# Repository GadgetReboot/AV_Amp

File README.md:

# AV_Amp
THS7316 three channel video buffer and stereo op amp audio buffer
<br><br><BR><BR>

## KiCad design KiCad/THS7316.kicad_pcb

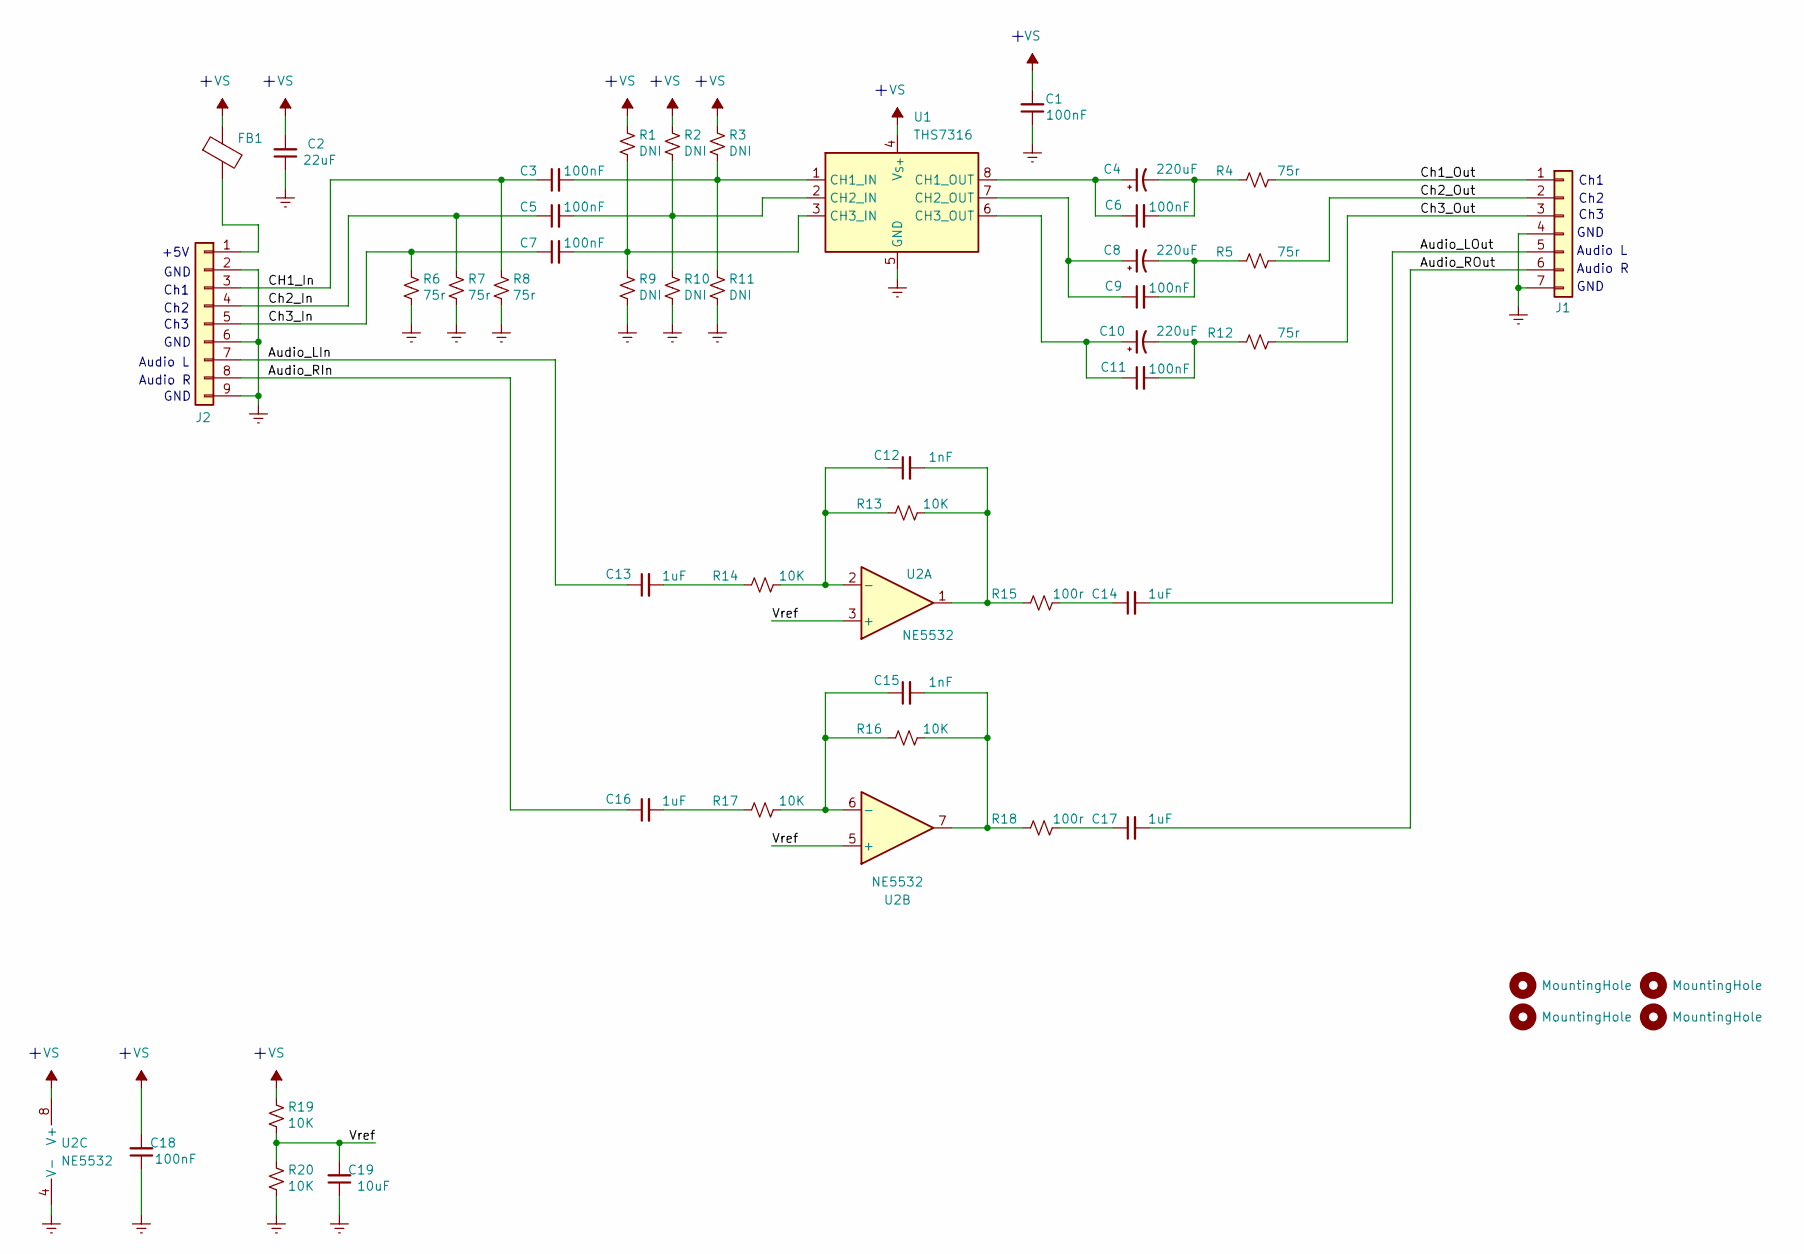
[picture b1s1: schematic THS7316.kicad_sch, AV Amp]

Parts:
C1, C3, C5, C6, C7, C9, C11, C18: 100nF; C_0805_2012Metric_Pad1.18x1.45mm_HandSolder
C2: 22uF; C_0805_2012Metric_Pad1.18x1.45mm_HandSolder
C4, C8, C10: 220uF; CP_Elec_6.3x7.7; MPN EDK227M010A9HAA
C12, C15: 1nF; C_0805_2012Metric_Pad1.18x1.45mm_HandSolder
C13, C14, C16, C17: 1uF; C_0805_2012Metric_Pad1.18x1.45mm_HandSolder
C19: 10uF; C_0805_2012Metric_Pad1.18x1.45mm_HandSolder
FB1: MPZ2012S331A; L_0805_TDK_MPZ2012S331A
H1, H2, H3, H4: MountingHole; MountingHole_3.5mm
J1: Conn_01x07; PinHeader_1x07_P2.54mm_Vertical
J2: Conn_01x09; PinHeader_1x09_P2.54mm_Vertical
R1, R2, R3, R9, R10, R11: DNI; R_0805_2012Metric_Pad1.20x1.40mm_HandSolder
R4, R5, R6, R7, R8, R12: 75r; R_0805_2012Metric_Pad1.20x1.40mm_HandSolder
R13, R14, R16, R17, R19, R20: 10K; R_0805_2012Metric_Pad1.20x1.40mm_HandSolder
R15, R18: 100r; R_0805_2012Metric_Pad1.20x1.40mm_HandSolder
U1: THS7316; SOIC-8_3.9x4.9mm_P1.27mm
U2: NE5532; SOIC-8_3.9x4.9mm_P1.27mm

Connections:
/Audio_LIn: C13.1, J2.7
/Audio_LOut: C14.2, J1.5
/Audio_RIn: C16.1, J2.8
/Audio_ROut: C17.2, J1.6
/CH1_In: C3.1, J2.3, R8.1
/Ch1_Out: J1.1, R4.2
/Ch2_In: C5.1, J2.4, R7.1
/Ch2_Out: J1.2, R5.2
/Ch3_In: C7.1, J2.5, R6.1
/Ch3_Out: J1.3, R12.2
/Vref: C19.2, R19.2, R20.1, U2.3 (+), U2.5 (+)
GNDREF: C1.1, C2.1, C18.1, C19.1, J1.4, J1.7, J2.2, J2.6, J2.9, R6.2, R7.2, R8.2, R9.2, R10.2, R11.2, R20.2, U1.5 (GND), U2.4 (V-)
unnamed: C4.2, C6.2, R4.1
unnamed: C8.2, C9.2, R5.1
unnamed: C10.2, C11.2, R12.1
unnamed: C12.2, R13.2, R15.1, U2.1
unnamed: C13.2, R14.1
unnamed: C14.1, R15.2
unnamed: C15.2, R16.2, R18.1, U2.7
unnamed: C16.2, R17.1
unnamed: C17.1, R18.2
unnamed: FB1.2, J2.1
unnamed: C3.2, R3.2, R11.1, U1.1 (CH1_IN)
unnamed: C4.1, C6.1, U1.8 (CH1_OUT)
unnamed: C5.2, R2.2, R10.1, U1.2 (CH2_IN)
unnamed: C8.1, C9.1, U1.7 (CH2_OUT)
unnamed: C7.2, R1.2, R9.1, U1.3 (CH3_IN)
unnamed: C10.1, C11.1, U1.6 (CH3_OUT)
unnamed: C12.1, R13.1, R14.2, U2.2 (-)
unnamed: C15.1, R16.1, R17.2, U2.6 (-)
VS: C1.2, C2.2, C18.2, FB1.1, R1.1, R2.1, R3.1, R19.1, U1.4 (V_{S+}), U2.8 (V+)

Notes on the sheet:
GND
Ch2
Ch1
Audio L
Ch3
+5V
Audio R

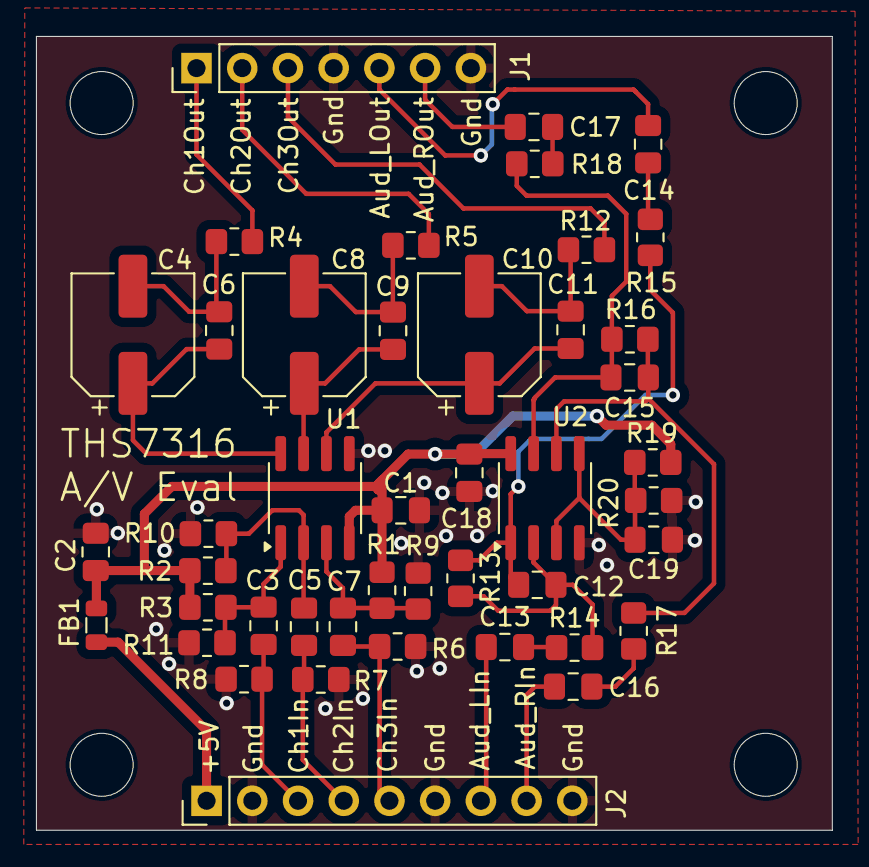
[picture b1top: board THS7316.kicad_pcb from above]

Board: 2 copper layers, 44.2 x 44.1 mm, 48 parts (0 on the bottom side), 31 nets.
